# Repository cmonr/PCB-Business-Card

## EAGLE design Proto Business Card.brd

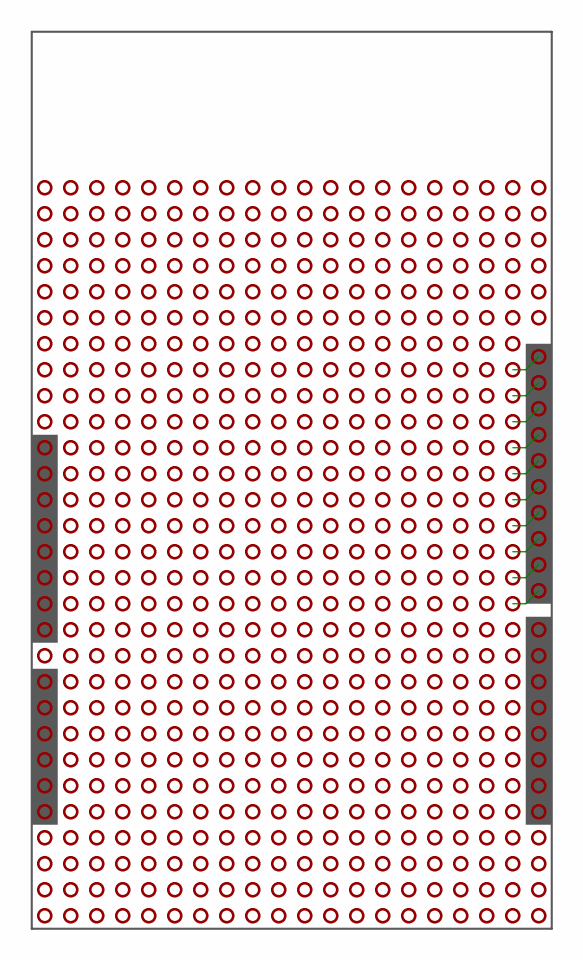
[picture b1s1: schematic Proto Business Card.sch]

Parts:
U$1, U$3, U$21, U$37, U$570, U$574: VIA.2-2.CORNER; 2-2.CORNER
U$2, U$4, U$5, U$6, U$7, U$8, U$9, U$10, U$11, U$12, U$13, U$14, U$15, U$16, U$17, U$18, U$19, U$20, U$22, U$23, U$24, U$25, U$26, U$27, U$28, U$29, U$30, U$31, U$32, U$33, U$34, U$35, U$36, U$45, U$46, U$77, U$78, U$112, U$113, U$120, U$121, U$122, U$123, U$124, U$125, U$145, U$146, U$150, U$152, U$153, U$170, U$182, U$183, U$211, U$212, U$240, U$241, U$269, U$270, U$298, U$299, U$327, U$328, U$356, U$357, U$385, U$386, U$414, U$415, U$443, U$444, U$472, U$473, U$501, U$502, U$530, U$531, U$559, U$560, U$566, U$567, U$568, U$569, U$571, U$572, U$573, U$575, U$588: VIA.3-3; 3-3
U$38, U$39, U$40, U$41, U$42, U$43, U$44, U$47, U$48, U$49, U$50, U$51, U$52, U$53, U$54, U$55, U$56, U$57, U$58, U$59, U$60, U$61, U$62, U$63, U$64, U$65, U$66, U$67, U$68, U$69, U$70, U$71, U$72, U$73, U$76, U$79, U$80, U$81, U$82, U$83, U$84, U$85, U$86, U$87, U$88, U$89, U$90, U$91, U$92, U$93, U$94, U$101, U$102, U$103, U$104, U$105, U$106, U$107, U$108, U$109, U$110, U$111, U$114, U$115, U$116, U$117, U$118, U$119, U$126, U$127, U$128, U$129, U$130, U$131, U$132, U$133, U$134, U$135, U$136, U$137, U$138, U$139, U$140, U$141, U$142, U$143, U$144, U$147, U$151, U$154, U$155, U$156, U$157, U$158, U$159, U$160, U$161, U$162, U$163, U$164, U$165, U$166, U$167, U$168, U$169, U$171, U$172, U$173, U$174, U$175, U$176, U$177, U$178, U$179, U$180, U$181, U$184, U$185, U$186, U$187, U$188, U$189, U$190, U$191, U$192, U$193, U$194, U$195, U$196, U$197, U$198, U$199, U$200, U$201, U$202, U$203, U$204, U$205, U$206, U$207, U$208, U$209, U$210, U$213, U$214, U$215, U$216, U$217, U$218, U$219, U$220, U$221, U$222, U$223, U$224, U$225, U$226, U$227, U$228, U$229, U$230, U$231, U$232, U$233, U$234, U$235, U$236, U$237, U$238, U$239, U$242, U$243, U$244, U$245, U$246, U$247, U$248, U$249, U$250, U$251, U$252, U$253, U$254, U$255, U$256, U$257, U$258, U$259, U$260, U$261, U$262, U$263, U$264, U$265, U$266, U$267, U$268, U$271, U$272, U$273, U$274, U$275, U$276, U$277, U$278, U$279, U$280, U$281, U$282, U$283, U$284, U$285, U$286, U$287, U$288, U$289, U$290, U$291, U$292, U$293, U$294, U$295, U$296, U$297, U$300, U$301, U$302, U$303, U$304, U$305, U$306, U$307, U$308, U$309, U$310, U$311, U$312, U$313, U$314, U$315, U$316, U$317, U$318, U$319, U$320, U$321, U$322, U$323, U$324, U$325, U$326, U$329, U$330, U$331, U$332, U$333, U$334, U$335, U$336, U$337, U$338, U$339, U$340, U$341, U$342, U$343, U$344, U$345, U$346, U$347, U$348, U$349, U$350, U$351, U$352, U$353, U$354, U$355, U$358, U$359, U$360, U$361, U$362, U$363, U$364, U$365, U$366, U$367, U$368, U$369, U$370, U$371, U$372, U$373, U$374, U$375, U$376, U$377, U$378, U$379, U$380, U$381, U$382, U$383, U$384, U$387, U$388, U$389, U$390, U$391, U$392, U$393, U$394, U$395, U$396, U$397, U$398, U$399, U$400, U$401, U$402, U$403, U$404, U$405, U$406, U$407, U$408, U$409, U$410, U$411, U$412, U$413, U$416, U$417, U$418, U$419, U$420, U$421, U$422, U$423, U$424, U$425, U$426, U$427, U$428, U$429, U$430, U$431, U$432, U$433, U$434, U$435, U$436, U$437, U$438, U$439, U$440, U$441, U$442, U$445, U$446, U$447, U$448, U$449, U$450, U$451, U$452, U$453, U$454, U$455, U$456, U$457, U$458, U$459, U$460, U$461, U$462, U$463, U$464, U$465, U$466, U$467, U$468, U$469, U$470, U$471, U$474, U$475, U$476, U$477, U$478, U$479, U$480, U$481, U$482, U$483, U$484, U$485, U$486, U$487, U$488, U$489, U$490, U$491, U$492, U$493, U$494, U$495, U$496, U$497, U$498, U$499, U$500, U$503, U$504, U$505, U$506, U$507, U$508, U$509, U$510, U$511, U$512, U$513, U$514, U$515, U$516, U$517, U$518, U$519, U$520, U$521, U$522, U$523, U$524, U$525, U$526, U$527, U$528, U$529, U$532, U$533, U$534, U$535, U$536, U$537, U$538, U$539, U$540, U$541, U$542, U$543, U$544, U$545, U$546, U$547, U$548, U$549, U$550, U$551, U$552, U$553, U$554, U$555, U$556, U$557, U$558, U$561, U$562, U$563, U$564, U$565, U$585, U$586, U$587: VIA.4-4; 4-4
U$74, U$75, U$95, U$96, U$97, U$98, U$99, U$100, U$148, U$149: VIA.NONE; NONE

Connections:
unnamed: U$99.VIA, U$145.VIA
unnamed: U$100.VIA, U$146.VIA
unnamed: U$97.VIA, U$124.VIA
unnamed: U$98.VIA, U$125.VIA
unnamed: U$95.VIA, U$122.VIA
unnamed: U$96.VIA, U$123.VIA
unnamed: U$74.VIA, U$120.VIA
unnamed: U$75.VIA, U$121.VIA
unnamed: U$148.VIA, U$150.VIA
unnamed: U$149.VIA, U$170.VIA

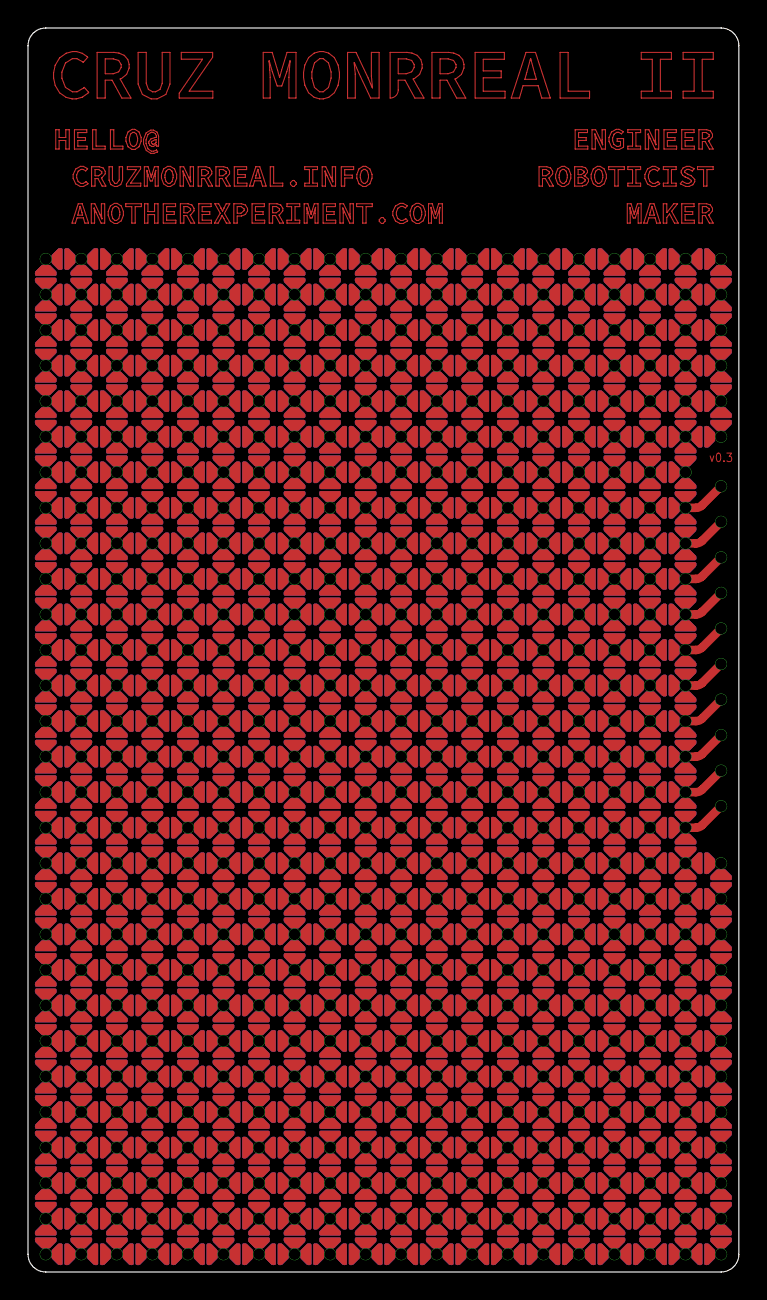
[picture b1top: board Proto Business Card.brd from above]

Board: 2 copper layers, 50.8 x 88.9 mm, 579 parts (0 on the bottom side), 10 nets.

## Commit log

2016-04-12 Initial commit of PCB. Flower Vias look solid.
2016-04-12 Generated preview images
2016-04-12 Renamed project
2016-05-16 Text is now on, and the grid is complete. Still missing example layers on the back
2016-05-20 Finally in a finished state!
2016-06-06 Modified flower pads to shrink spacing, remove msak between pads, and shrink the via thickness. Added silk to the Arduino headers, and removed the K-Map text combinations in the back
2016-06-15 Corrected bStop layer. Shrunk via thickness to 2 mils.
2016-06-16 Actually corrected via thickness issue. Also fixed the silk version.

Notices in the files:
parts and their libraries:
microbuilder: This work is placed in the public domain, and may be freely used for commercial and non-commercial work with the following conditions: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
